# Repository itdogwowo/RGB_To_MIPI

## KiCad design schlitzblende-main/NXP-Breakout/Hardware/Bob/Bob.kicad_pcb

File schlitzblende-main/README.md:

# Project Schlitzblende

**Sushi-ya Demo**

## RE Touchbar for fun

Touchbar is the Applespeak for their "DFR" (Dynamic Function Row ?) module on the old MacBook Pro computers. It's a touch screen that replaces the function keys with an extreme aspect ratio that can't be found anywhere else.

I personally love exotic stuff, and I believe this can be used in a lot of places such as custom keyboards. So here comes the project. We were able to reverse engineer the interface and make it work on a NXP devboard. The English video is not up yet. You can checkout the Chinese version first if you're interested.

[https://www.bilibili.com/video/BV1494y1w7jn/](https://www.bilibili.com/video/BV1494y1w7jn/)

Long story short, it's a MIPI-DSI display that has a non-standard long command 0x3C to send the video data with automated address increment. The initialization sequence does contain some secret, non-standard commands, but the display seems to work just fine without them. The screen does not support video mode at all, it's a command-only display.

Don't be intimidated by MIPI-DSI. People have already replicated our work in a couple of days, made the display work in HS using a SSD2805 bridge and ESP32! (Image Credit: [借来的猫w](https://space.bilibili.com/1637994))

The touchscreen RE is yet to be done. It's using the same Broadcom multi-touch ASIC found on other Apple products.

## Hardware Info

### A1706

- **Internal Model Number:** AMS983JC01F1A
- **Manufacturer:** Samsung
- **Type:** OLED
- **Width:** 60 pixels
- **Height:** 2170 pixels
- **Pixel format:** 24-bit RGB

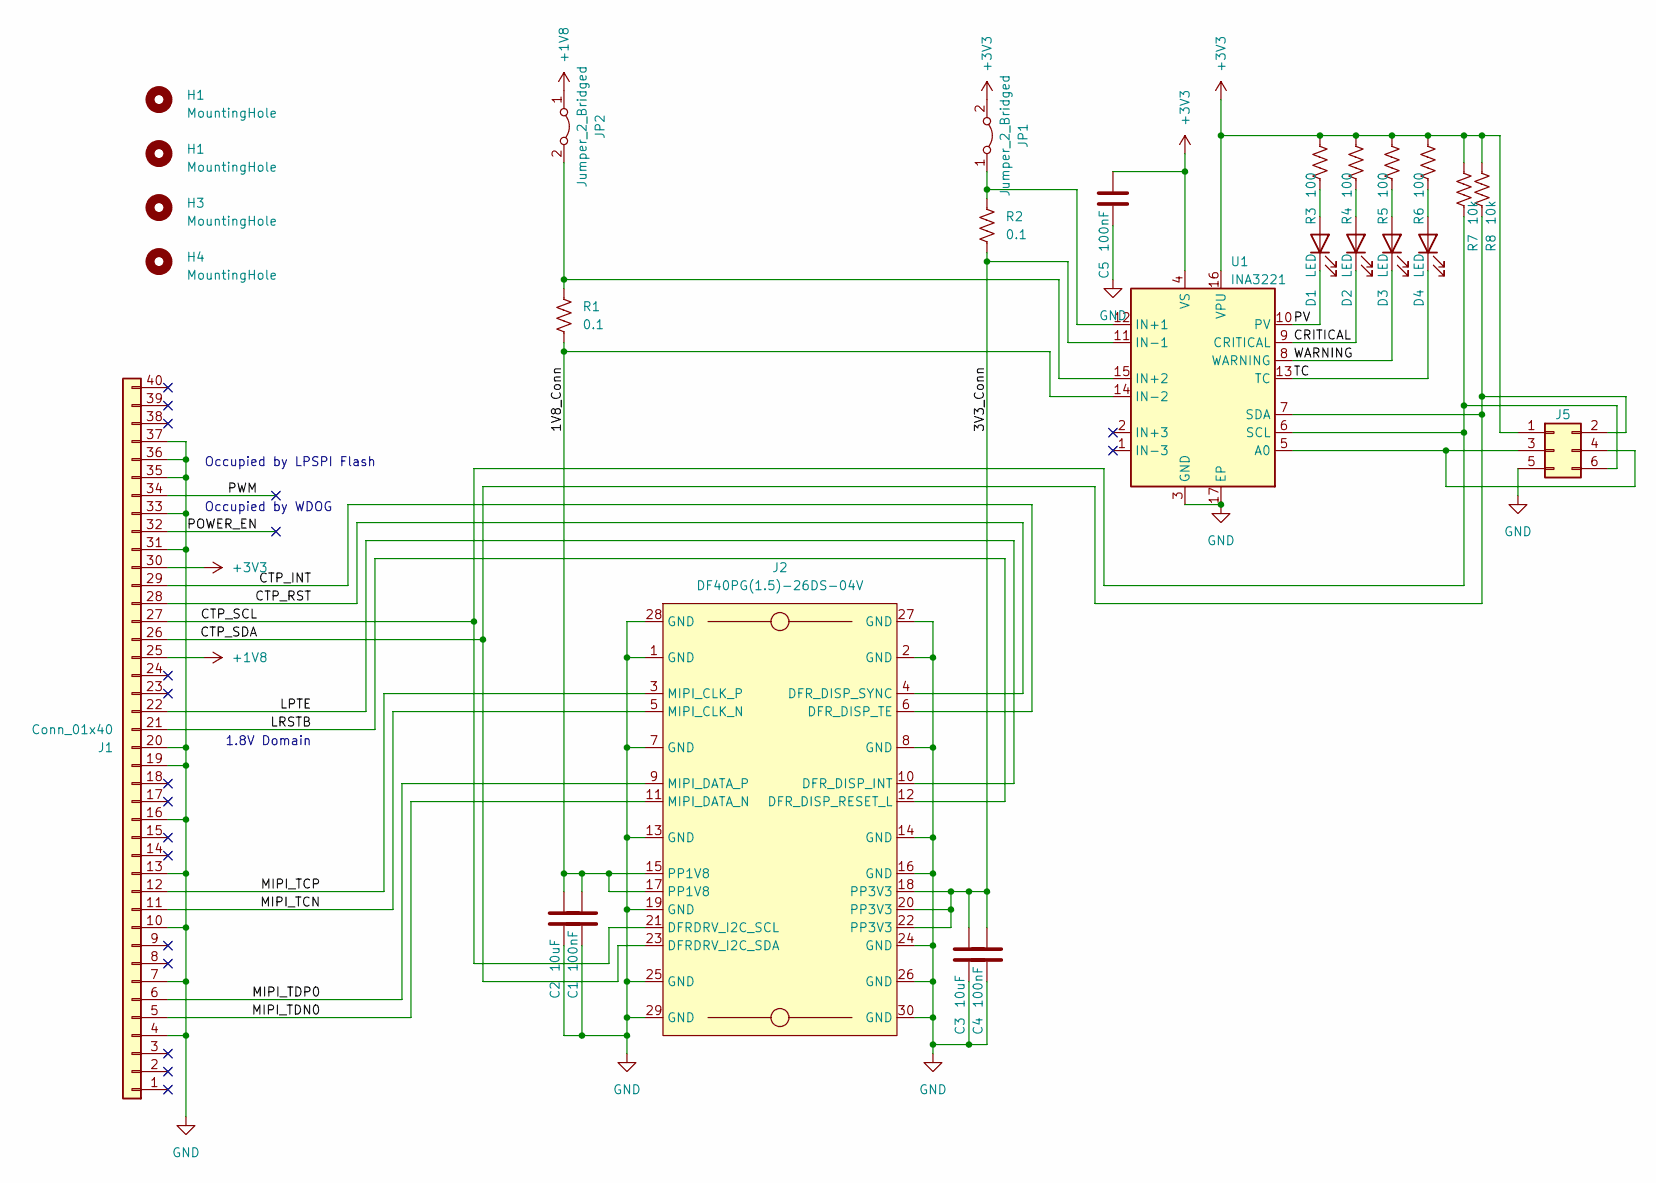
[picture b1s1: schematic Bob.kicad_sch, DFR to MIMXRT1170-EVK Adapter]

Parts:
C1, C4, C5: 100nF; C_0805_2012Metric
C2, C3: 10uF; C_0805_2012Metric
D1, D2, D3, D4: LED; D_0603_1608Metric_Pad1.05x0.95mm_HandSolder
H1, H3, H4: MountingHole; MountingHole_2.2mm_M2_DIN965
J1: Conn_01x40; TE_4-1734839-0_1x40-1MP_P0.5mm_Horizontal
J2: DF40PG(1.5)-26DS-04V
J5: Conn_02x03_Odd_Even; PinHeader_2x03_P2.54mm_Vertical
JP1, JP2: Jumper_2_Bridged; PinHeader_1x02_P2.54mm_Vertical
R1, R2: 0.1; LED_0805_2012Metric
R3, R4, R5, R6: 100; LED_0603_1608Metric
R7, R8: 10k; LED_0603_1608Metric
U1: INA3221; Texas_RGV_S-PVQFN-N16_EP2.1x2.1mm

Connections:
+1V8: J1.25, JP2.1 (A)
+3V3: C5.1, J1.30, J5.1, JP1.2 (B), R3.1, R4.1, R5.1, R6.1, R7.1, R8.1, U1.4 (VS), U1.16 (VPU)
/1V8_Conn: C1.1, C2.1, J2.15 (PP1V8), J2.17 (PP1V8), R1.2, U1.14 (IN-2)
/3V3_Conn: C3.1, C4.1, J2.18 (PP3V3), J2.20 (PP3V3), J2.22 (PP3V3), R2.2, U1.11 (IN-1)
/CRITICAL: D2.1 (K), U1.9 (CRITICAL)
/CTP_INT: J1.29, J2.6 (DFR_DISP_TE)
/CTP_RST: J1.28, J2.4 (DFR_DISP_SYNC)
/CTP_SCL: J1.27, J2.21 (DFRDRV_I2C_SCL), J5.6, R7.2, U1.6 (SCL)
/CTP_SDA: J1.26, J2.23 (DFRDRV_I2C_SDA), J5.2, R8.2, U1.7 (SDA)
/LPTE: J1.22, J2.10 (DFR_DISP_INT)
/LRSTB: J1.21, J2.12 (DFR_DISP_RESET_L)
/MIPI_TCN: J1.11, J2.5 (MIPI_CLK_N)
/MIPI_TCP: J1.12, J2.3 (MIPI_CLK_P)
/MIPI_TDN0: J1.5, J2.11 (MIPI_DATA_N)
/MIPI_TDP0: J1.6, J2.9 (MIPI_DATA_P)
/POWER_EN: J1.32
/PV: D1.1 (K), U1.10 (PV)
/PWM: J1.34
/TC: D4.1 (K), U1.13 (TC)
/WARNING: D3.1 (K), U1.8 (WARNING)
GND: C1.2, C2.2, C3.2, C4.2, C5.2, J1.4, J1.7, J1.10, J1.13, J1.16, J1.19, J1.20, J1.31, J1.33, J1.35, J1.36, J1.37, J2.1 (GND), J2.2 (GND), J2.7 (GND), J2.8 (GND), J2.13 (GND), J2.14 (GND), J2.16 (GND), J2.19 (GND), J2.24 (GND), J2.25 (GND), J2.26 (GND), J2.27 (GND), J2.28 (GND), J2.29 (GND), J2.30 (GND), J5.5, U1.3 (GND), U1.17 (EP)
unnamed: D1.2 (A), R3.2
unnamed: D2.2 (A), R4.2
unnamed: D3.2 (A), R5.2
unnamed: D4.2 (A), R6.2
unnamed: J5.3, J5.4, U1.5 (A0)
unnamed: JP1.1 (A), R2.1, U1.12 (IN+1)
unnamed: JP2.2 (B), R1.1, U1.15 (IN+2)

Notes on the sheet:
Occupied by WDOG
1.8V Domain
Occupied by LPSPI Flash

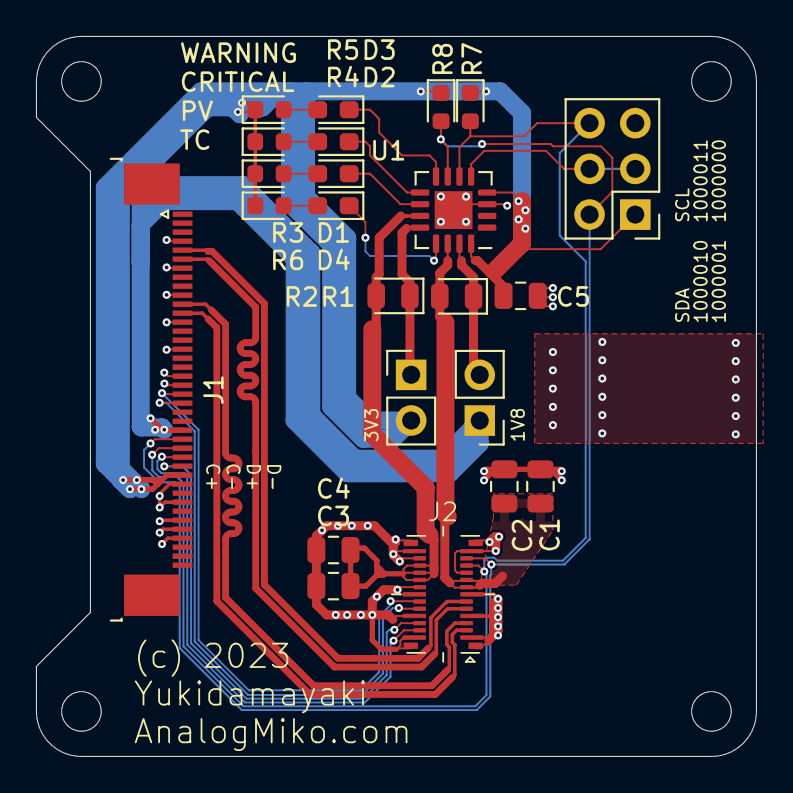
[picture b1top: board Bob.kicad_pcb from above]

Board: 2 copper layers, 40.0 x 40.0 mm, 27 parts (0 on the bottom side), 26 nets.

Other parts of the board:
H2: MountingHole; MountingHole_2.2mm_M2_DIN965

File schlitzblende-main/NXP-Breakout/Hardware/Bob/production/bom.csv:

Designator,Footprint,Quantity,Value,LCSC Part #
"C1, C4, C5",0805,3,100nF,
"C2, C3",0805,2,10uF,
"D1, D2, D3, D4",0603,4,LED,
"H1, H2, H3, H4",MountingHole_2.2mm_M2_DIN965,4,MountingHole,
J1,TE_4-1734839-0_1x40-1MP_P0.5mm_Horizontal,1,Conn_01x40,
J2,DF40PG(1.5)-26DS-04V,1,DF40PG(1.5)-26DS-04V,
J5,PinHeader_2x03_P2.54mm_Vertical,1,Conn_02x03_Odd_Even,
"JP1, JP2",PinHeader_1x02_P2.54mm_Vertical,2,Jumper_2_Bridged,
"R1, R2",0805,2,0.1,
"R3, R4, R5, R6",0603,4,100,
"R7, R8",0603,2,10k,
U1,Texas_RGV_S-PVQFN-N16_EP2.1x2.1mm,1,INA3221,

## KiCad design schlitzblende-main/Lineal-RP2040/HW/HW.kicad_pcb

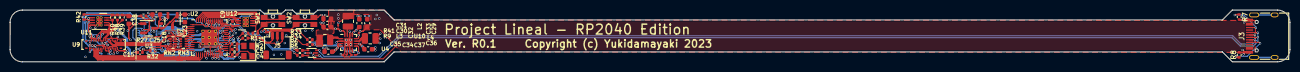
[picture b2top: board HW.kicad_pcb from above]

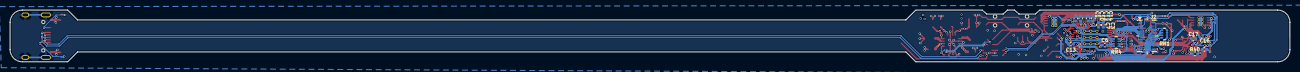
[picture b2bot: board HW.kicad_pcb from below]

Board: 4 copper layers, 260.0 x 10.5 mm, 65 parts (14 on the bottom side), 77 nets.

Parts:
C1, C13, C14, C15, C16, C17, C18: 1uF; C_0402_1005Metric
C3, C6, C7, C9, C10, C12: 100nF; C_0402_1005Metric
C4, C5: 18pF; C_0402_1005Metric
C23, C25, C29, C30, C31, C33, C35, C36: 10uF; C_0603_1608Metric
C32, C34: 100nF; C_0201_0603Metric
C37: 10nF/DNP; C_0201_0603Metric
C38: 100nF; C_0603_1608Metric
J2: AA07-S022VA1; AA07-S022VA1-Mockup
J3: USB_C_Receptacle_USB2.0; USB_C_Receptacle_HRO_TYPE-C-31-M-12
J5: SM03B-SRSS-TB; JST_SH_SM03B-SRSS-TB_1x03-1MP_P1.00mm_Horizontal
L2: 10uH; L_1008_2520Metric
L3, L4: 4.7uH; L_1008_2520Metric
R1, R2: 1K; R_0402_1005Metric
R5, R6: 27; R_0402_1005Metric
R7, R8: 5.1K; R_0402_1005Metric
R9, R40, R41: 0; R_0402_1005Metric
R10, R42: 10K; R_0402_1005Metric
R27: DNP; R_0402_1005Metric
R32: 4.7K/DNP; R_0402_1005Metric
R33, R34: 100; R_0402_1005Metric
R38, R39: 4.7K; R_0402_1005Metric
RN1: 4.7K; R_Array_Convex_4x0402
RN2: 120; R_Array_Convex_4x0402
RN3: 110; R_Array_Convex_4x0402
RN4: 60; R_Array_Convex_4x0402
SW1, SW2: EVQP7C; SW_SPST_EVQP7C
U2: RP2040; RP2040-QFN-56
U3: XC6206P182MR; SOT-23-3
U4: USBLC6-2P6; SOT-666
U7: XC6206P332MR; SOT-23-3
U9: DFR_A1706_Internal_Conn; CONN_BM28B0.6-34DS&slash_2-0.35V53_HIR
U10: TPS65632; QFN-16-1EP_3x3mm_P0.5mm_EP1.7x1.7mm
U11, U12: W25Q40EW, USON2x3; WSON-8-1EP_3x3mm_P0.5mm_EP1.2x2mm_ThermalVias
Y1: 12MHz; Oscillator_SMD_Abracon_ASE-4Pin_3.2x2.5mm

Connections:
+1V1: C10.1, C12.1, C14.1, U2.23 (DVDD), U2.45 (VREG_VOUT), U2.50 (DVDD)
+1V8: C3.1, C6.1, C7.1, C9.1, C13.1, C15.1, C16.1, C38.1, J2.20 (PP1V8), J2.21 (PP1V8), R10.1, R27.1, R32.1, R38.1, R39.1, R42.1, RN1.5 (R4.2), RN1.6 (R3.2), RN1.7 (R2.2), RN1.8 (R1.2), U2.1 (IOVDD), U2.10 (IOVDD), U2.22 (IOVDD), U2.33 (IOVDD), U2.42 (IOVDD), U2.49 (IOVDD), U3.2 (VO), U9.18 (+1V8), U11.8 (VCC), U12.8 (VCC)
+3V3: C1.1, C17.1, C18.1, C25.1, U2.43 (ADC_AVDD), U2.44 (VREG_IN), U2.48 (USB_VDD), U3.3 (VI), U7.2 (VO), U9.22 (+3V3)
/DFR_CN: RN2.6 (R3.2), RN3.7 (R2.2), RN4.2 (R2.1), U9.25 (MIPI_C-)
/DFR_CP: RN2.5 (R4.2), RN3.8 (R1.2), RN4.1 (R1.1), U9.23 (MIPI_C+)
/DFR_DN: RN2.8 (R1.2), RN3.5 (R4.2), RN4.4 (R4.1), U9.31 (MIPI_D-)
/DFR_DP: RN2.7 (R2.2), RN3.6 (R3.2), RN4.3 (R3.1), U9.29 (MIPI_D+)
/DFR_I2C_SCL: R39.2, U2.28 (GPIO17), U9.19 (DFR_SDA)
/DFR_I2C_SDA: R38.2, U2.27 (GPIO16), U9.17 (DFR_SCL)
/DFR_INT: U2.16 (GPIO13), U9.10 (DFR_INT)
/DFR_POWER_EN: R9.2, U2.41 (GPIO29_ADC3)
/DFR_RSTB: U2.17 (GPIO14), U9.8 (DFR_RSTB)
/DFR_SWIRE: U2.18 (GPIO15), U9.6 (STOD_SWIRE)
/DFR_TE: U2.14 (GPIO11), U9.14 (DFR_TE)
/DFR_VSYNC: J2.3 (DISP_VSYNC), U2.15 (GPIO12), U9.12 (DFR_VSYNC)
/HSCN: RN3.2 (R2.1), U2.11 (GPIO8)
/HSCP: RN3.1 (R1.1), U2.12 (GPIO9)
/HSDN: RN3.4 (R4.1), U2.8 (GPIO6)
/HSDP: RN3.3 (R3.1), U2.9 (GPIO7)
/LPDN: RN4.6 (R3.2), U2.38 (GPIO26_ADC0)
/LPDP: RN4.5 (R4.2), U2.39 (GPIO27_ADC1)
/LPPU: RN4.7 (R2.2), RN4.8 (R1.2), U2.34 (GPIO22)
/PANEL_DETECT: J2.1 (PANEL_DETECT), R27.2, U2.5 (GPIO3)
/QSPI_SCLK: U2.52 (QSPI_SCLK), U12.6 (CLK)
/QSPI_SD0: U2.53 (QSPI_SD0), U12.5 (DI(IO0))
/QSPI_SD1: U2.55 (QSPI_SD1), U12.2 (DO(IO1))
/QSPI_SD2: U2.54 (QSPI_SD2), U12.3 (IO2)
/QSPI_SD3: U2.51 (QSPI_SD3), U12.7 (IO3)
/QSPI_SS: R1.1, U2.56 (QSPI_SS), U12.1 (~CS)
/RP2_SWIRE: R41.2, U2.40 (GPIO28_ADC2)
/RUN: SW2.1, U2.26 (RUN)
/SC/RX: J5.1, R33.2
/SD/TX: J5.3, R34.2
/SWCLK: R33.1, U2.24 (SWCLK)
/SWD: R34.1, U2.25 (SWD)
/TP_CLK: J2.9 (SPI_CLK_R), U2.4 (GPIO2)
/TP_CLKIN_~RST: J2.15 (CLKIN_RESET_L), U2.6 (GPIO4)
/TP_GPIO2: J2.4 (GPIO2), U2.37 (GPIO25)
/TP_I2C_SCL: J2.16 (ROM_I2C_SDA), RN1.2 (R2.1), U2.29 (GPIO18)
/TP_I2C_SDA: J2.14 (ROM_I2C_SCL), RN1.1 (R1.1), U2.31 (GPIO20)
/TP_LID: J2.2 (LID), U2.36 (GPIO24)
/TP_MISO: J2.7 (SPI_MISO_R), U2.2 (GPIO0)
/TP_MOSI: J2.10 (SPI_MOSI_R), U2.30 (GPIO19)
/TP_ROM_WC: J2.19 (ROM_WC), R32.2, U2.7 (GPIO5)
/TP_~CS: J2.8 (SPI_CS_L), U2.32 (GPIO21)
/TP_~INT: J2.13 (INT_L), RN1.4 (R4.1), U2.3 (GPIO1)
/TP_~RESET: J2.18 (RESET_L), RN1.3 (R3.1), U2.13 (GPIO10)
/USB_DN: R6.2, U2.46 (USB_DM)
/USB_DP: R5.2, U2.47 (USB_DP)
/USB_PRE_DN: J3.A7 (D-), J3.B7 (D-), U4.6 (I/O1)
/USB_PRE_DP: J3.A6 (D+), J3.B6 (D+), U4.4 (I/O2)
/VHIGH: C33.2, U9.26 (STOD_V1), U10.13 (OUTP2)
/VNEG: C36.2, U9.32 (STOD_V3), U10.10 (OUTN)
/VPOS: C35.2, U9.30 (STOD_V2), U10.3 (OUTP1), U10.4 (FBS)
/XIN: C4.1, U2.20 (XIN), Y1.1
/XOUT: R2.1, U2.21 (XOUT)
GND: C1.2, C3.2, C4.2, C5.2, C6.2, C7.2, C9.2, C10.2, C12.2, C13.2, C14.2, C15.2, C16.2, C17.2, C18.2, C23.2, C25.2, C29.1, C30.1, C31.1, C32.1, C33.1, C34.1, C35.1, C36.1, C37.1, C38.2, J2.5 (GND), J2.6 (GND), J2.11 (GND), J2.12 (GND), J2.17 (GND), J2.23 (GND), J2.24 (GND), J2.25 (GND), J2.26 (GND), J3.A1 (GND), J3.A12 (GND), J3.B1 (GND), J3.B12 (GND), J3.S1 (SHIELD), J5.2, L4.2, R7.2, R8.2, R40.1, RN2.1 (R1.1), RN2.2 (R2.1), RN2.3 (R3.1), RN2.4 (R4.1), SW1.2, SW2.2, U2.19 (TESTEN), U2.57 (GND), U3.1 (GND), U4.2 (GND), U7.1 (GND), U9.1 (GND), U9.2 (GND), U9.15 (GND), U9.20 (GND), U9.21 (GND), U9.24 (GND), U9.27 (GND), U9.28 (GND), U9.33 (GND), U9.34 (GND), U10.2 (PGND1), U10.5 (SELP2), U10.7 (AGND), U10.14 (PGND2), U10.17 (EP), U11.4 (GND), U12.4 (GND), Y1.2, Y1.4
unnamed: C5.1, R2.2, Y1.3
unnamed: J3.A5 (CC1), R8.1
unnamed: J3.B5 (CC2), R7.1
unnamed: R1.2, SW1.1
unnamed: R5.1, U4.3 (I/O2)
unnamed: R6.1, U4.1 (I/O1)
unnamed: R40.2, U9.16 (MYSTERY)
unnamed: C34.2, U10.6 (CT)
unnamed: C37.2, R41.1, U10.9 (CTRL)
unnamed: R9.1, U10.8 (EN)
unnamed: L4.1, U10.11 (SWN)
unnamed: L3.2, U10.1 (SWP1)
unnamed: L2.1, U10.15 (SWP2)
unnamed: U9.13 (F_CLK), U11.6 (CLK)
unnamed: U9.9 (F_DIO/IO0), U11.5 (DI(IO0))
unnamed: U9.7 (F_D0/IO1), U11.2 (DO(IO1))
unnamed: U9.5 (F_~WP/IO2), U11.3 (IO2)
unnamed: R10.2, U9.3 (F_~HOLD/IO3), U11.7 (IO3)
unnamed: R42.2, U9.11 (F_~CS), U11.1 (~CS)
VBUS: C23.1, C29.2, C30.2, C31.2, C32.2, J2.22 (PP5V), J3.A4 (VBUS), J3.A9 (VBUS), J3.B4 (VBUS), J3.B9 (VBUS), L2.2, L3.1, U4.5 (VBUS), U7.3 (VI), U10.12 (PVIN), U10.16 (AVIN)

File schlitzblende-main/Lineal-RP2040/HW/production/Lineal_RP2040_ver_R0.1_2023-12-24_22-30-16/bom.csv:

Designator,Footprint,Quantity,Value,LCSC Part #
"C1, C13, C14, C15, C16, C17, C18",0402,7,1uF,
"C10, C12, C3, C6, C7, C9",0402,6,100nF,
"C23, C25, C29, C30, C31, C33, C35, C36",0603,8,10uF,
"C32, C34",0201,2,100nF,
C37,0201,1,10nF/DNP,
C38,0603,1,100nF,
"C4, C5",0402,2,18pF,
J2,AA07-S022VA1-Mockup,1,AA07-S022VA1,
J3,USB_C_Receptacle_HRO_TYPE-C-31-M-12,1,USB_C_Receptacle_USB2.0,
J5,JST_SH_SM03B-SRSS-TB_1x03-1MP_P1.00mm_Horizontal,1,SM03B-SRSS-TB,
L2,1008,1,10uH,
"L3, L4",1008,2,4.7uH,
"R1, R2",0402,2,1K,
"R10, R42",0402,2,10K,
R27,0402,1,DNP,
R32,0402,1,4.7K/DNP,
"R33, R34",0402,2,100,
"R38, R39",0402,2,4.7K,
"R40, R41, R9",0402,3,0,
"R5, R6",0402,2,27,
"R7, R8",0402,2,5.1K,
RN1,R_Array_Convex_4x0402,1,4.7K,
RN2,R_Array_Convex_4x0402,1,120,
RN3,R_Array_Convex_4x0402,1,110,
RN4,R_Array_Convex_4x0402,1,60,
"SW1, SW2",SW_SPST_EVQP7C,2,EVQP7C,
U10,QFN-16-1EP_3x3mm_P0.5mm_EP1.7x1.7mm,1,TPS65632,
"U11, U12",WSON-8-1EP_3x3mm_P0.5mm_EP1.2x2mm_ThermalVias,2,"W25Q40EW, USON2x3",
U2,RP2040-QFN-56,1,RP2040,
U3,SOT-23-3,1,XC6206P182MR,
U4,SOT-666,1,USBLC6-2P6,
U7,SOT-23-3,1,XC6206P332MR,
U9,CONN_BM28B0.6-34DS&slash_2-0.35V53_HIR,1,DFR_A1706_Internal_Conn,
Y1,Oscillator_SMD_Abracon_ASE-4Pin_3.2x2.5mm,1,12MHz,

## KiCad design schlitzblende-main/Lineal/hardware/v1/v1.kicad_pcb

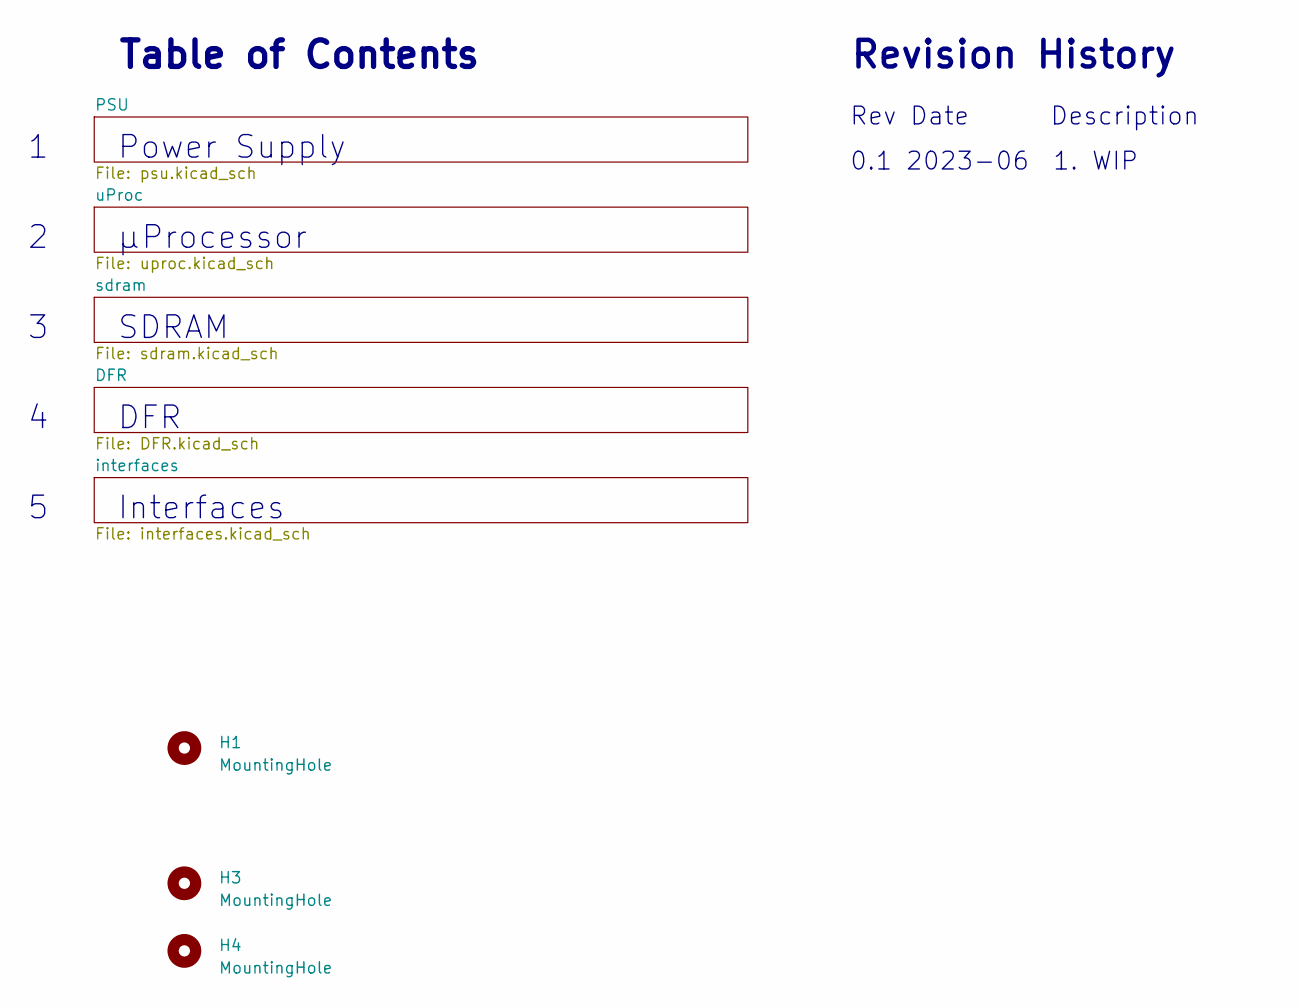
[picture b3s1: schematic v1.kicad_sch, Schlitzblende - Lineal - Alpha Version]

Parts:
H1, H3, H4: MountingHole; MountingHole_2.2mm_M2_DIN965

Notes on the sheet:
DFR
1. WIP
Revision History
SDRAM
Rev Date Description
0.1 2023-06
Table of Contents
Power Supply
Interfaces
µProcessor

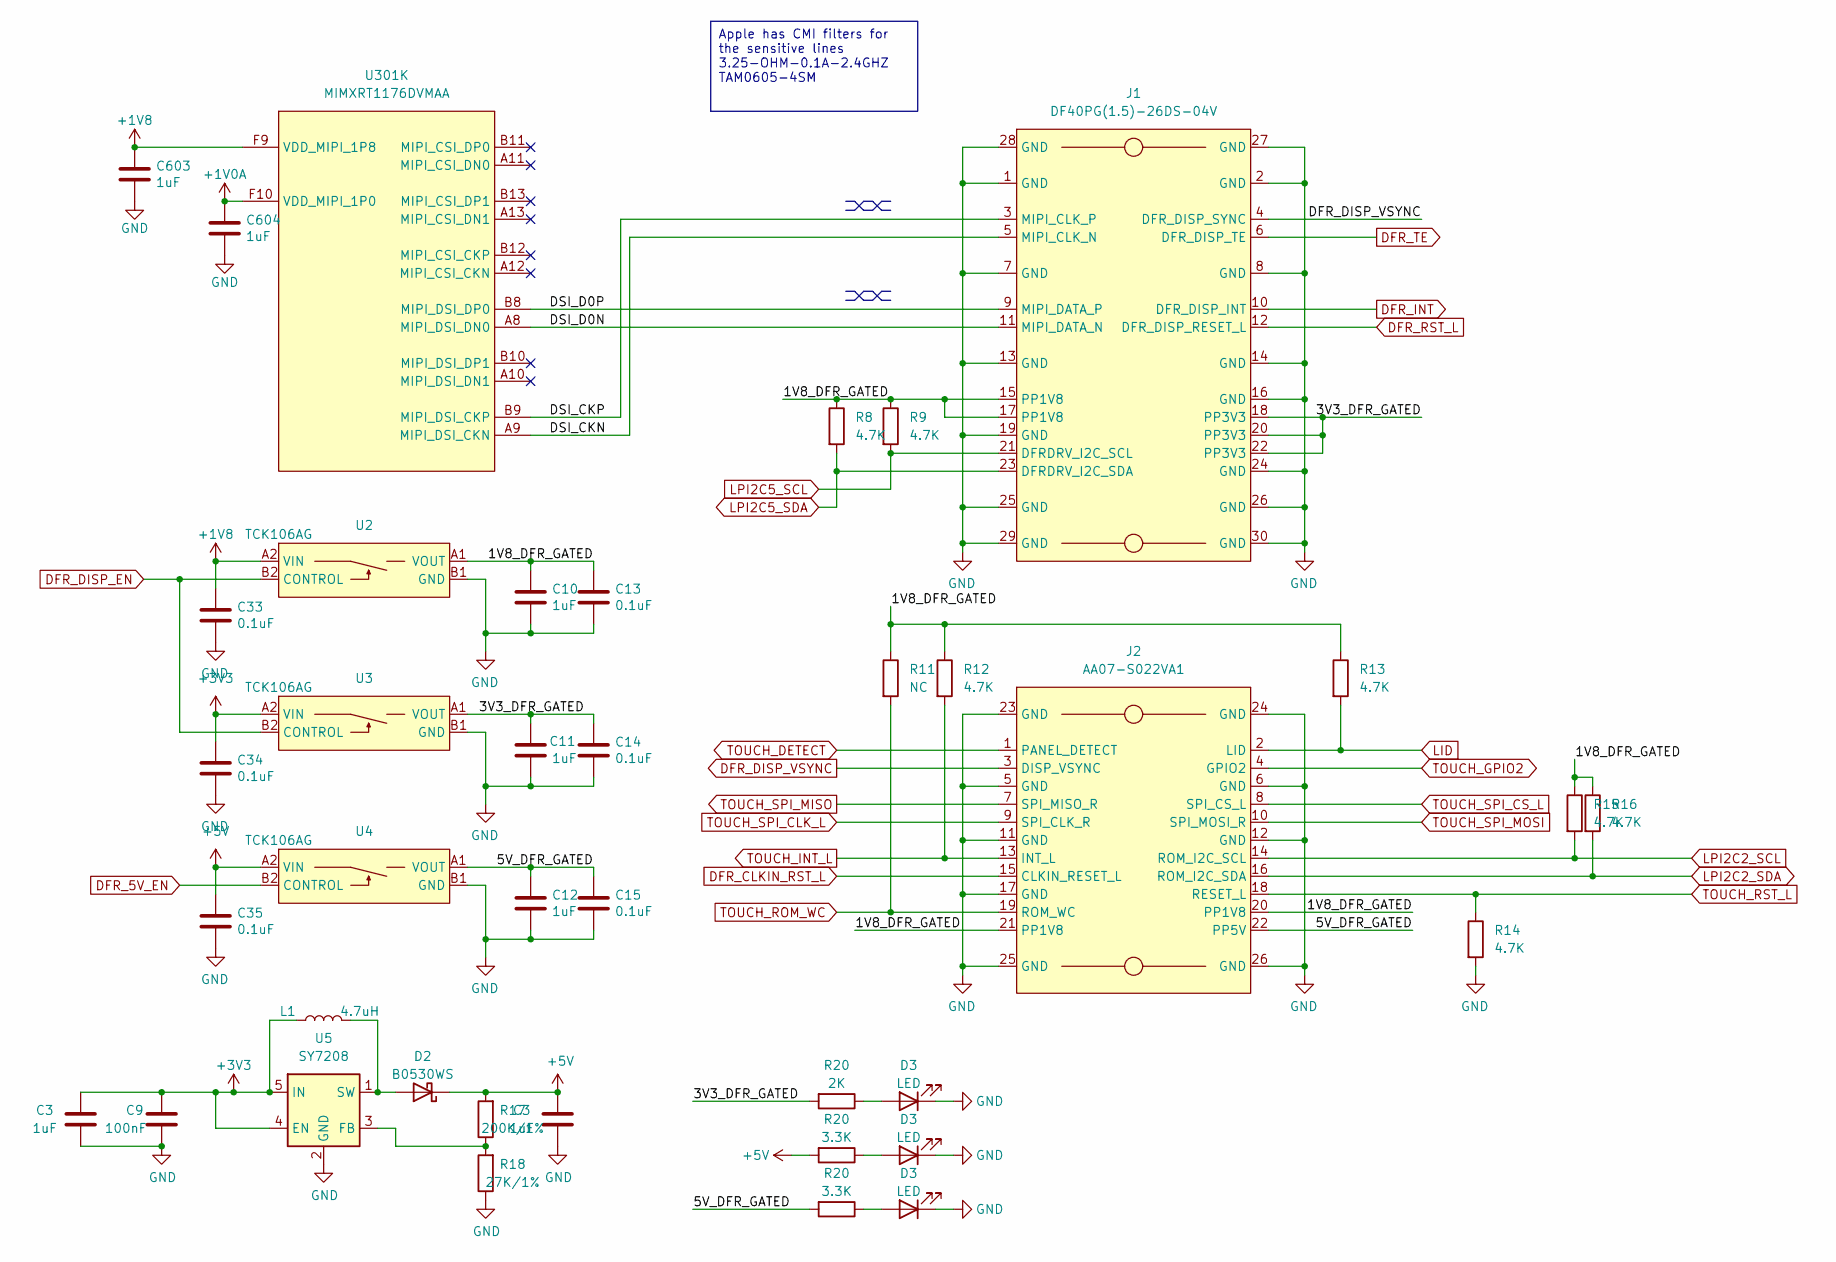
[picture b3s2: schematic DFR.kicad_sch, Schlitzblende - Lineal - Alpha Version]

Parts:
C3, C10, C11, C12, C603, C604: 1uF; C_0402_1005Metric
C9: 100nF; C_0402_1005Metric
C13, C14, C15, C33, C34, C35: 0.1uF; C_0402_1005Metric
D2: B0530WS; D_SOD-523
D3: LED; D_0402_1005Metric
J1: DF40PG(1.5)-26DS-04V
J2: AA07-S022VA1; AA07-S022VA1-Mockup
L1: 4.7uH; L_1008_2520Metric
R8, R9, R12, R13, R14, R15, R16: 4.7K; R_0402_1005Metric
R11: NC; R_0402_1005Metric
R17: 200K/1%; R_0402_1005Metric
R18: 27K/1%; R_0402_1005Metric
R20: 2K; R_0402_1005Metric
U2, U3, U4: TCK106AG; WLCSP-4_0.8x0.8mm_P0.4mm
U5: SY7208; SOT-23-6
U301: MIMXRT1176DVMAA; BGA-289_17x17_14.0x14.0mm

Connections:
+1V0A: C604.1, U301.F10 (VDD_MIPI_1P0); also elsewhere on the board
+1V8: C33.1, C603.1, U2.A2 (VIN), U301.F9 (VDD_MIPI_1P8); also elsewhere on the board
/DFR/1V8_DFR_GATED: C10.1, C13.1, J1.15 (PP1V8), J1.17 (PP1V8), J2.20 (PP1V8), J2.21 (PP1V8), R8.1, R9.1, R11.1, R12.1, R13.1, R15.1, R16.1, U2.A1 (VOUT)
/DFR/DSI_CKN: J1.5 (MIPI_CLK_N), U301.A9 (MIPI_DSI_CKN)
/DFR/DSI_CKP: J1.3 (MIPI_CLK_P), U301.B9 (MIPI_DSI_CKP)
/DFR/DSI_D0N: J1.11 (MIPI_DATA_N), U301.A8 (MIPI_DSI_DN0)
/DFR/DSI_D0P: J1.9 (MIPI_DATA_P), U301.B8 (MIPI_DSI_DP0)
DFR_5V_EN: U4.B2 (CONTROL); also elsewhere on the board
DFR_CLKIN_RST_L: J2.15 (CLKIN_RESET_L); also elsewhere on the board
DFR_DISP_EN: U2.B2 (CONTROL), U3.B2 (CONTROL); also elsewhere on the board
DFR_DISP_VSYNC: J1.4 (DFR_DISP_SYNC), J2.3 (DISP_VSYNC); also elsewhere on the board
DFR_INT: J1.10 (DFR_DISP_INT); also elsewhere on the board
DFR_RST_L: J1.12 (DFR_DISP_RESET_L); also elsewhere on the board
DFR_TE: J1.6 (DFR_DISP_TE); also elsewhere on the board
LID: J2.2 (LID), R13.2; also elsewhere on the board
LPI2C2_SCL: J2.14 (ROM_I2C_SCL), R15.2; also elsewhere on the board
LPI2C2_SDA: J2.16 (ROM_I2C_SDA), R16.2; also elsewhere on the board
LPI2C5_SCL: J1.21 (DFRDRV_I2C_SCL), R9.2
LPI2C5_SDA: J1.23 (DFRDRV_I2C_SDA), R8.2
unnamed: D2.2 (A), L1.2, U5.1 (SW)
unnamed: D3.2 (A), R20.1
unnamed: R17.1, R18.2, U5.3 (FB)
TOUCH_DETECT: J2.1 (PANEL_DETECT); also elsewhere on the board
TOUCH_GPIO2: J2.4 (GPIO2); also elsewhere on the board
TOUCH_INT_L: J2.13 (INT_L), R12.2; also elsewhere on the board
TOUCH_ROM_WC: J2.19 (ROM_WC), R11.2; also elsewhere on the board
TOUCH_RST_L: J2.18 (RESET_L), R14.1; also elsewhere on the board
TOUCH_SPI_CLK_L: J2.9 (SPI_CLK_R); also elsewhere on the board
TOUCH_SPI_CS_L: J2.8 (SPI_CS_L); also elsewhere on the board
TOUCH_SPI_MISO: J2.7 (SPI_MISO_R); also elsewhere on the board
TOUCH_SPI_MOSI: J2.10 (SPI_MOSI_R); also elsewhere on the board

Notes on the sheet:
Apple has CMI filters for the sensitive lines 3.25-OHM-0.1A-2.4GHZ TAM0605-4SM

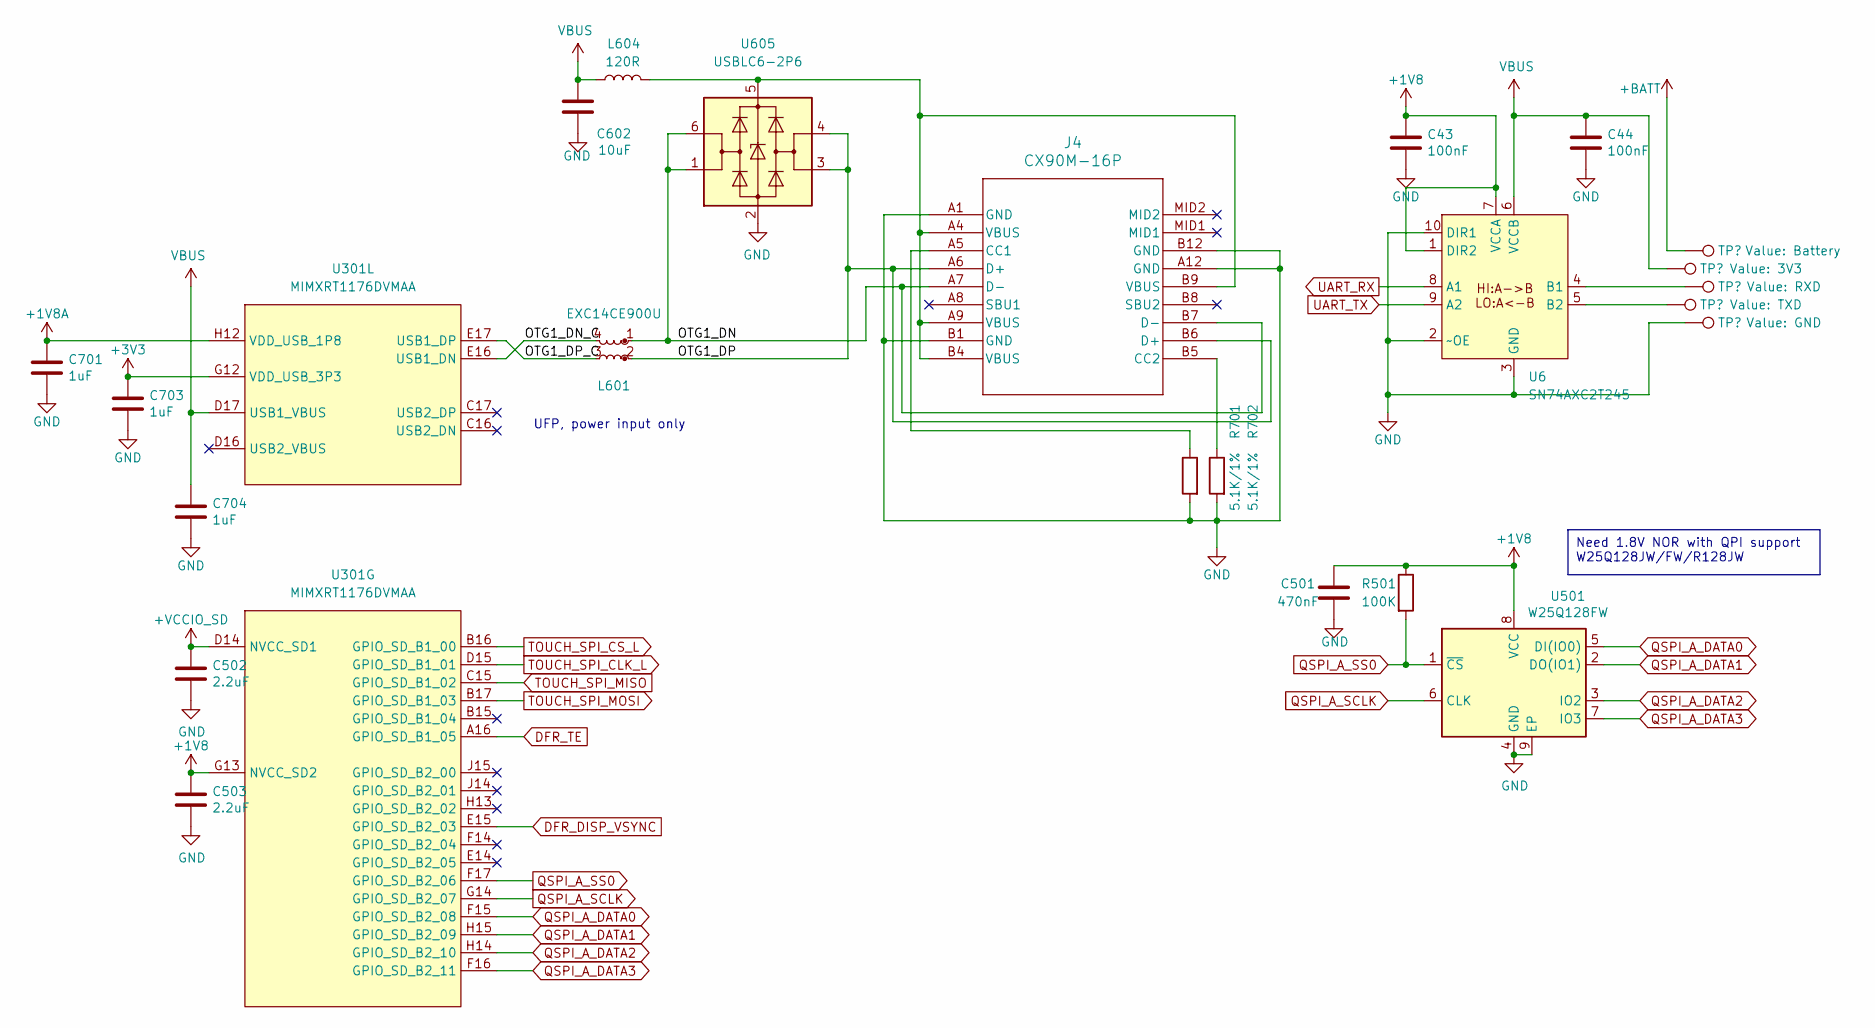
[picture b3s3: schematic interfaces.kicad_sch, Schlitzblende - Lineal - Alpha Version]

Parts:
C43, C44: 100nF; C_0402_1005Metric
C501: 470nF; C_0402_1005Metric
C502, C503: 2.2uF; C_0402_1005Metric
C602: 10uF; C_0603_1608Metric
C701, C703, C704: 1uF; C_0402_1005Metric
J4: CX90M-16P; CX90M-16P_HIR
L601: EXC14CE900U; L_CommonModeChoke_Panasonic_EXC14CE
L604: 120R; L_0603_1608Metric
R501: 100K; R_0402_1005Metric
R701, R702: 5.1K/1%; R_0402_1005Metric
TP5: 3V3; TestPoint_Pad_D1.0mm
TP6: TXD; TestPoint_Pad_D1.0mm
TP7: RXD; TestPoint_Pad_D1.0mm
TP8: GND; TestPoint_Pad_D1.0mm
TP9: Battery; TestPoint_Pad_D1.0mm
U6: SN74AXC2T245; UQFN-10_1.4x1.8mm_P0.4mm
U301: MIMXRT1176DVMAA; BGA-289_17x17_14.0x14.0mm
U501: W25Q128FW; WSON-8-1EP_6x5mm_P1.27mm_EP3.4x4.3mm
U605: USBLC6-2P6; SOT-666

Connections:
+1V8: C43.1, C501.2, C503.1, R501.1, U6.1 (DIR2), U6.7 (VCCA), U301.G13 (NVCC_SD2), U501.8 (VCC); also elsewhere on the board
+1V8A: C701.1, U301.H12 (VDD_USB_1P8); also elsewhere on the board
+BATT: TP9.1; also elsewhere on the board
+VCCIO_SD: C502.1, U301.D14 (NVCC_SD1); also elsewhere on the board
/interfaces/OTG1_DN: J4.A7 (D-), J4.B7 (D-), L601.1, U605.1 (I/O1), U605.6 (I/O1)
/interfaces/OTG1_DN_C: L601.4, U301.E16 (USB1_DN)
/interfaces/OTG1_DP: J4.A6 (D+), J4.B6 (D+), L601.2, U605.3 (I/O2), U605.4 (I/O2)
/interfaces/OTG1_DP_C: L601.3, U301.E17 (USB1_DP)
DFR_DISP_VSYNC: U301.E15 (GPIO_SD_B2_03); also elsewhere on the board
DFR_TE: U301.A16 (GPIO_SD_B1_05); also elsewhere on the board
unnamed: J4.A5 (CC1), R701.1
unnamed: J4.B5 (CC2), R702.1
unnamed: TP7.1, U6.4 (B1)
unnamed: TP6.1, U6.5 (B2)
unnamed: J4.A4 (VBUS), J4.A9 (VBUS), J4.B4 (VBUS), J4.B9 (VBUS), L604.2, U605.5 (VBUS)
QSPI_A_DATA0: U301.F15 (GPIO_SD_B2_08), U501.5 (DI(IO0))
QSPI_A_DATA1: U301.H15 (GPIO_SD_B2_09), U501.2 (DO(IO1))
QSPI_A_DATA2: U301.H14 (GPIO_SD_B2_10), U501.3 (IO2)
QSPI_A_DATA3: U301.F16 (GPIO_SD_B2_11), U501.7 (IO3)
QSPI_A_SCLK: U301.G14 (GPIO_SD_B2_07), U501.6 (CLK)
QSPI_A_SS0: R501.2, U301.F17 (GPIO_SD_B2_06), U501.1 (~CS)
TOUCH_SPI_CLK_L: U301.D15 (GPIO_SD_B1_01); also elsewhere on the board
TOUCH_SPI_CS_L: U301.B16 (GPIO_SD_B1_00); also elsewhere on the board
TOUCH_SPI_MISO: U301.C15 (GPIO_SD_B1_02); also elsewhere on the board
TOUCH_SPI_MOSI: U301.B17 (GPIO_SD_B1_03); also elsewhere on the board
UART_RX: U6.8 (A1); also elsewhere on the board
UART_TX: U6.9 (A2); also elsewhere on the board
VBUS: C44.1, C602.1, C704.1, L604.1, TP5.1, U6.6 (VCCB), U301.D17 (USB1_VBUS); also elsewhere on the board

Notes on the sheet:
Need 1.8V NOR with QPI support W25Q128JW/FW/R128JW
UFP, power input only

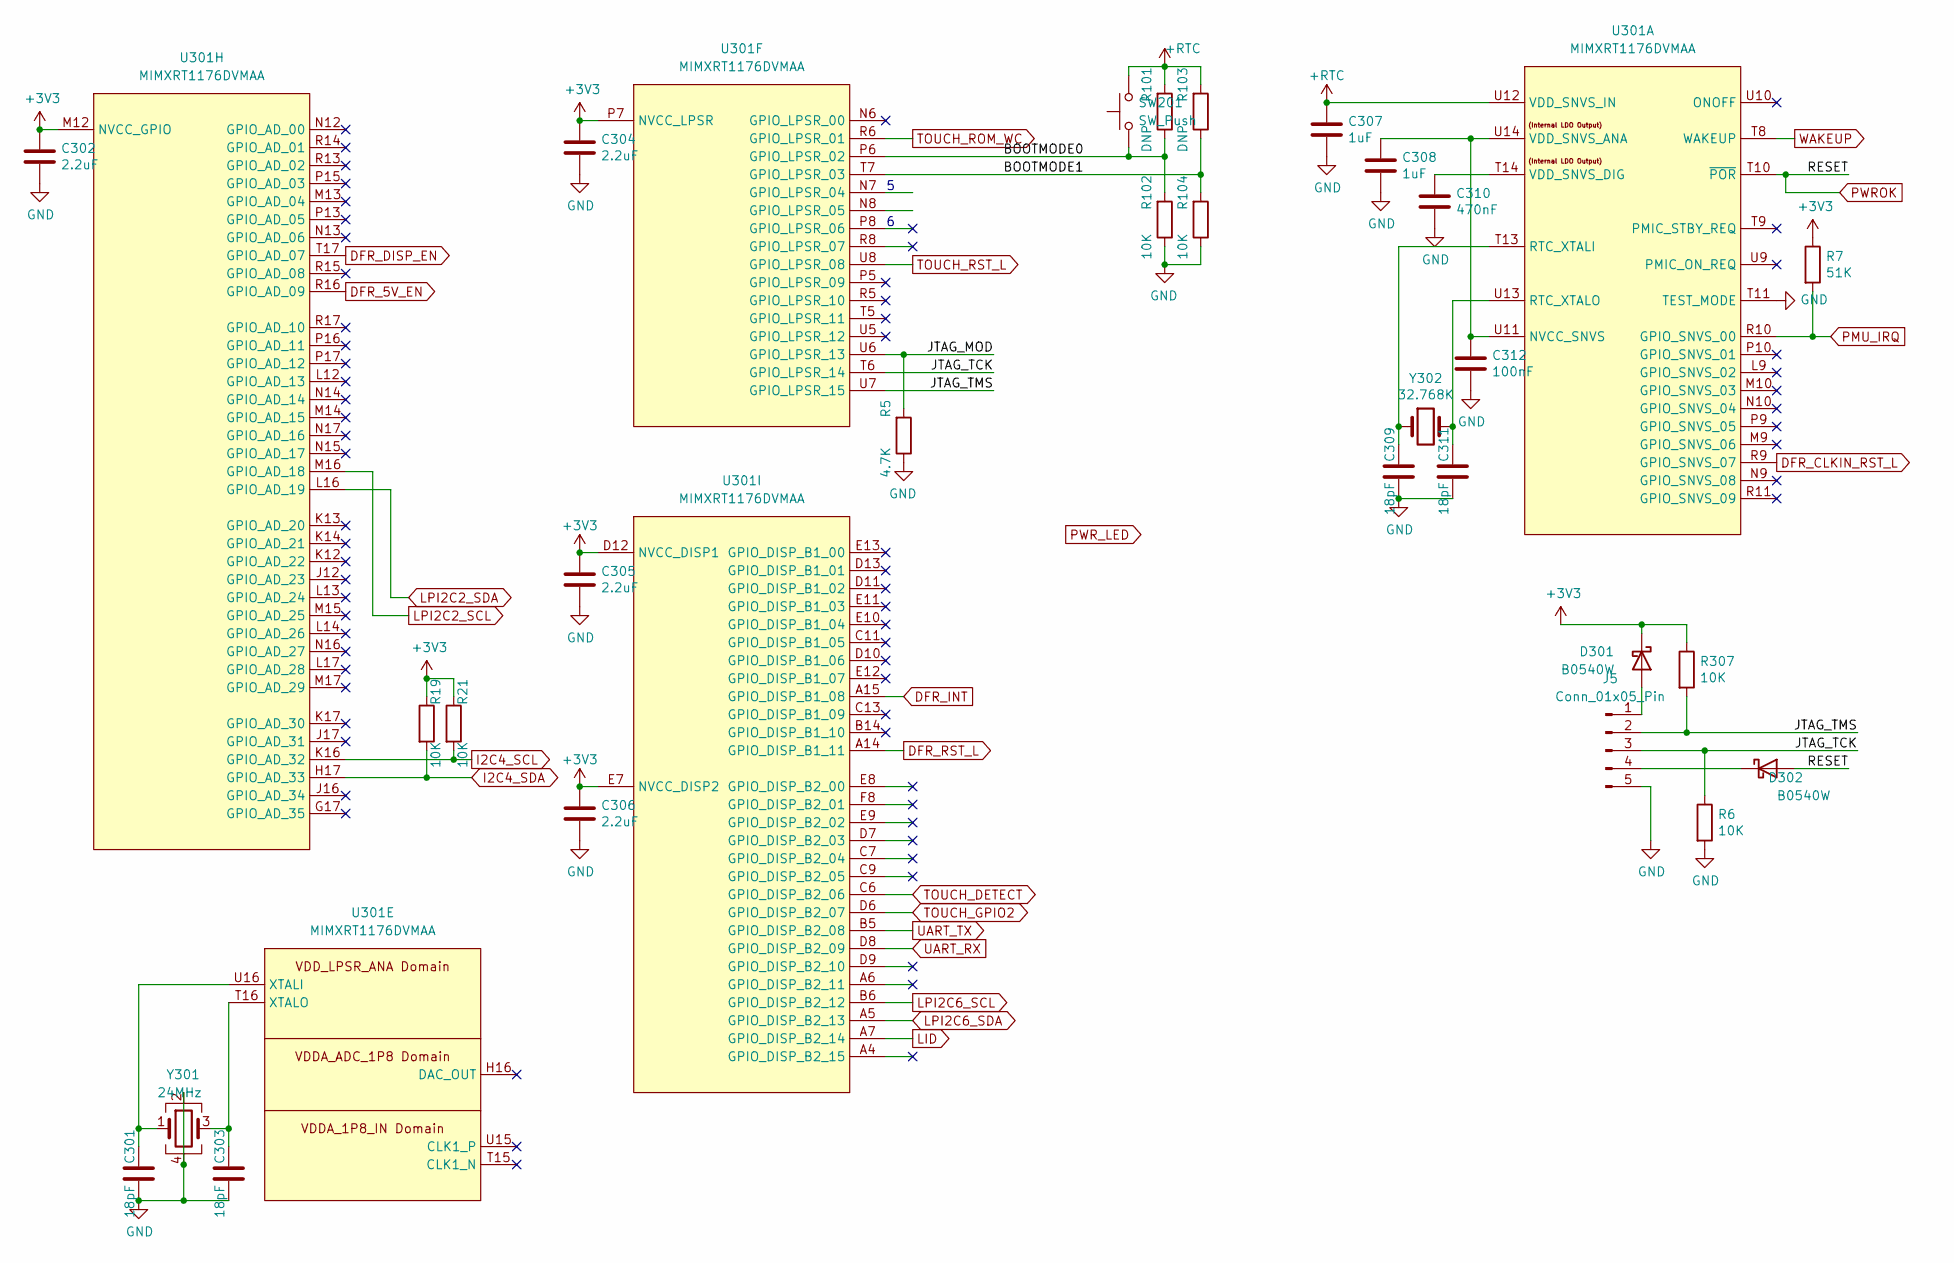
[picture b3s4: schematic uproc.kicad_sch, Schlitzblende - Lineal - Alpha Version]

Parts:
C301, C303, C309, C311: 18pF; C_0402_1005Metric
C302, C304, C305, C306: 2.2uF; C_0402_1005Metric
C307, C308: 1uF; C_0402_1005Metric
C310: 470nF; C_0402_1005Metric
C312: 100nF; C_0402_1005Metric
D301, D302: B0540W; D_SOD-323
J5: Conn_01x05_Pin; PinHeader_1x05_P1.27mm_Vertical_SMD
R5: 4.7K; R_0402_1005Metric
R6, R19, R21, R102, R104, R307: 10K; R_0402_1005Metric
R7: 51K; R_0402_1005Metric
R101, R103: DNP; R_0402_1005Metric
SW201: SW_Push; SW_SPST_TL3342
U301: MIMXRT1176DVMAA; BGA-289_17x17_14.0x14.0mm
Y301: 24MHz; Oscillator_SMD_Abracon_ASE-4Pin_3.2x2.5mm
Y302: 32.768K; Crystal_SMD_TXC_9HT11-2Pin_2.0x1.2mm_HandSoldering

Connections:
/uProc/BOOTMODE1: R103.1, R104.2, U301.T7 (GPIO_LPSR_03)
/uProc/JTAG_MOD: R5.2, U301.U6 (GPIO_LPSR_13)
/uProc/JTAG_TCK: J5.3, R6.1, U301.T6 (GPIO_LPSR_14)
/uProc/JTAG_TMS: J5.2, R307.2, U301.U7 (GPIO_LPSR_15)
DFR_5V_EN: U301.R16 (GPIO_AD_09); also elsewhere on the board
DFR_CLKIN_RST_L: U301.R9 (GPIO_SNVS_07); also elsewhere on the board
DFR_DISP_EN: U301.T17 (GPIO_AD_07); also elsewhere on the board
DFR_INT: U301.A15 (GPIO_DISP_B1_08); also elsewhere on the board
DFR_RST_L: U301.A14 (GPIO_DISP_B1_11); also elsewhere on the board
I2C4_SCL: R21.2, U301.K16 (GPIO_AD_32); also elsewhere on the board
I2C4_SDA: R19.2, U301.H17 (GPIO_AD_33); also elsewhere on the board
LID: U301.A7 (GPIO_DISP_B2_14); also elsewhere on the board
LPI2C2_SCL: U301.M16 (GPIO_AD_18); also elsewhere on the board
LPI2C2_SDA: U301.L16 (GPIO_AD_19); also elsewhere on the board
LPI2C6_SCL: U301.B6 (GPIO_DISP_B2_12)
LPI2C6_SDA: U301.A5 (GPIO_DISP_B2_13)
unnamed: D301.2 (A), J5.1
unnamed: D302.1 (K), J5.4
unnamed: C308.1, C312.1, U301.U11 (NVCC_SNVS), U301.U14 (VDD_SNVS_ANA)
unnamed: C309.2, U301.T13 (RTC_XTALI), Y302.1
unnamed: C311.2, U301.U13 (RTC_XTALO), Y302.2
unnamed: C310.1, U301.T14 (VDD_SNVS_DIG)
unnamed: C301.1, U301.U16 (XTALI), Y301.1
unnamed: C303.1, U301.T16 (XTALO), Y301.3
PMU_IRQ: R7.2, U301.R10 (GPIO_SNVS_00); also elsewhere on the board
PWROK: D302.2 (A), U301.T10 (~POR); also elsewhere on the board
TOUCH_DETECT: U301.C6 (GPIO_DISP_B2_06); also elsewhere on the board
TOUCH_GPIO2: U301.D6 (GPIO_DISP_B2_07); also elsewhere on the board
TOUCH_ROM_WC: U301.R6 (GPIO_LPSR_01); also elsewhere on the board
TOUCH_RST_L: U301.U8 (GPIO_LPSR_08); also elsewhere on the board
UART_RX: U301.D8 (GPIO_DISP_B2_09); also elsewhere on the board
UART_TX: U301.B5 (GPIO_DISP_B2_08); also elsewhere on the board
WAKEUP: U301.T8 (WAKEUP)

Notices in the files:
schlitzblende-main/Lineal-RP2040/HW/HW.kicad_pcb:
Copyright 2023 Yukidamayaki
This source describes Open Hardware and is licensed under the CERN-OHL-S v2.
Ver. R0.1 Copyright (c) Yukidamayaki 2023
schlitzblende-main/NXP-Breakout/Hardware/Bob/Bob.kicad_pcb:
(c) 2023
schlitzblende-main/NXP-Breakout/Hardware/Bob/Bob.kicad_sch:
Copyright 2023 Yukidamayaki @ AnalogMiko.com
